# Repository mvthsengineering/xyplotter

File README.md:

# xyplotter
An X-Y plotter with stepper motors for both axis and stepper control for pen height.

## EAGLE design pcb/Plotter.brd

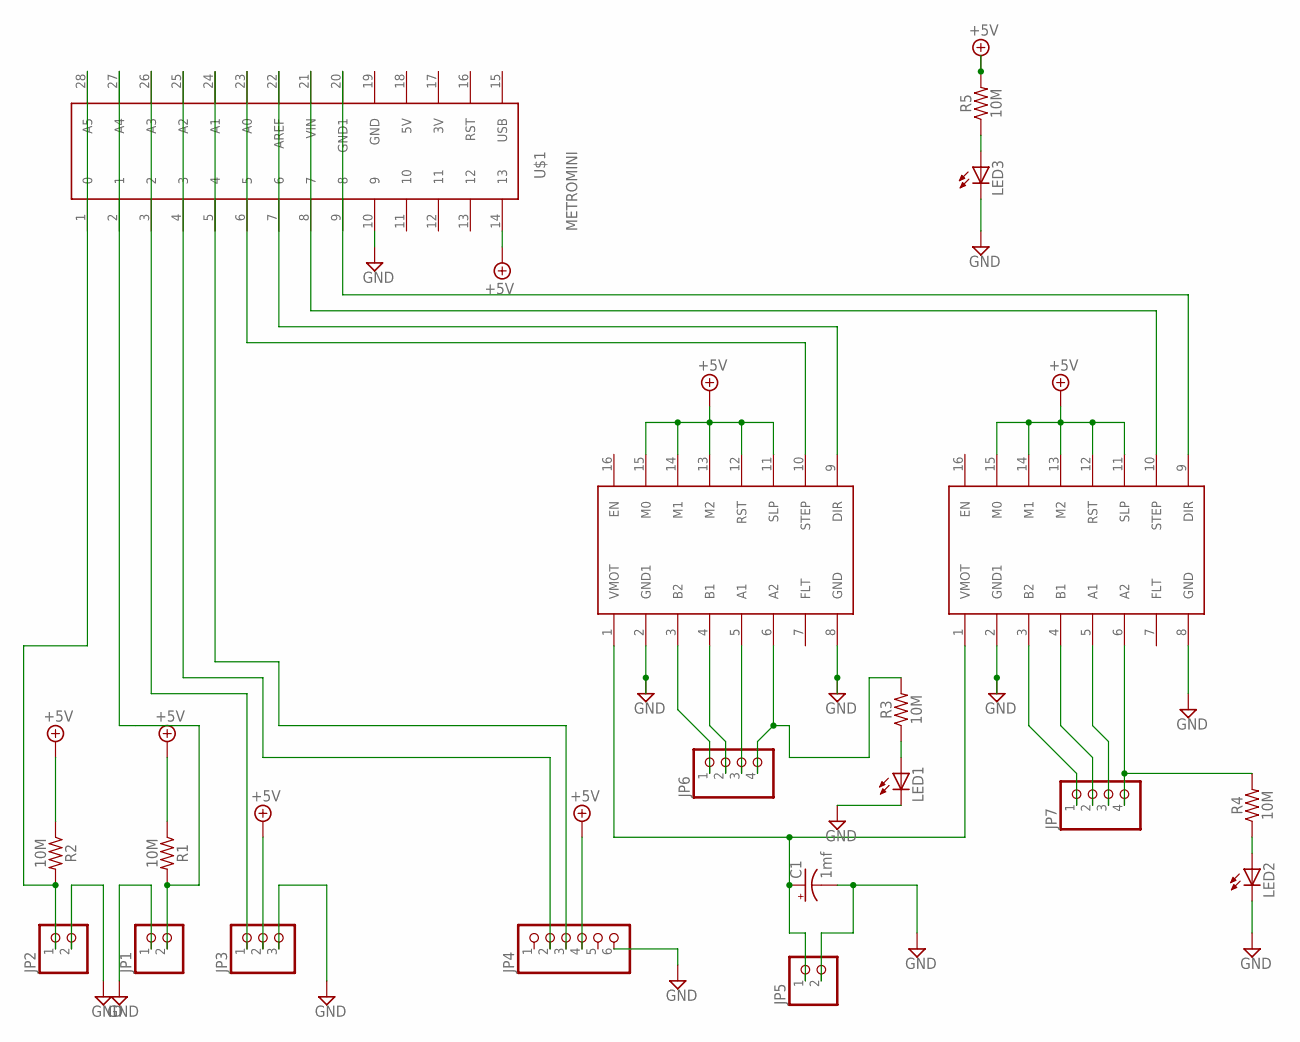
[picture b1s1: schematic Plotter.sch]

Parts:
C1: 1mf; CPOL-RADIAL-5MM-10MM-KIT
JP1, JP2, JP5: PINHD-1X2; 1X02
JP3: PINHD-1X3; 1X03
JP4: PINHD-1X6; 1X06
JP6, JP7: PINHD-1X4; 1X04
LED1, LED2, LED3: LED_ELD260; LED_LD260
R1, R2, R3, R4, R5: 10M; AXIAL-0.3
U$1: METROMINI
U$2, U$3: DRV8825

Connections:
+5V: JP3.2, JP4.4, R1.P$1 (1), R2.P$1 (1), R5.P$2 (2), U$1.14 (13), U$2.11 (SLP), U$2.12 (RST), U$2.13 (M2), U$2.14 (M1), U$2.15 (M0), U$3.11 (SLP), U$3.12 (RST), U$3.13 (M2), U$3.14 (M1), U$3.15 (M0)
GND: C1.-, JP1.1, JP2.2, JP3.3, JP4.6, JP5.2, LED1.K (C), LED2.K (C), LED3.K (C), U$1.10 (9), U$2.2 (GND1), U$2.8 (GND), U$3.2 (GND1), U$3.8 (GND)
unnamed: JP1.2, R1.P$2 (2), U$1.27 (A4)
unnamed: JP2.1, R2.P$2 (2), U$1.28 (A5)
unnamed: LED1.A, R3.P$1 (1)
unnamed: LED2.A, R4.P$1 (1)
unnamed: JP3.1, U$1.26 (A3)
unnamed: LED3.A, R5.P$1 (1)
unnamed: JP4.2, U$1.25 (A2)
unnamed: C1.+, JP5.1, U$2.1 (VMOT), U$3.1 (VMOT)
unnamed: JP4.3, U$1.24 (A1)
unnamed: JP6.1, U$2.3 (B2)
unnamed: JP6.2, U$2.4 (B1)
unnamed: JP6.3, U$2.5 (A1)
unnamed: JP6.4, R3.P$2 (2), U$2.6 (A2)
unnamed: JP7.1, U$3.3 (B2)
unnamed: JP7.2, U$3.4 (B1)
unnamed: JP7.3, U$3.5 (A1)
unnamed: JP7.4, R4.P$2 (2), U$3.6 (A2)
unnamed: U$1.21 (VIN), U$3.10 (STEP)
unnamed: U$1.23 (A0), U$2.10 (STEP)
unnamed: U$1.22 (AREF), U$2.9 (DIR)
unnamed: U$1.20 (GND1), U$3.9 (DIR)

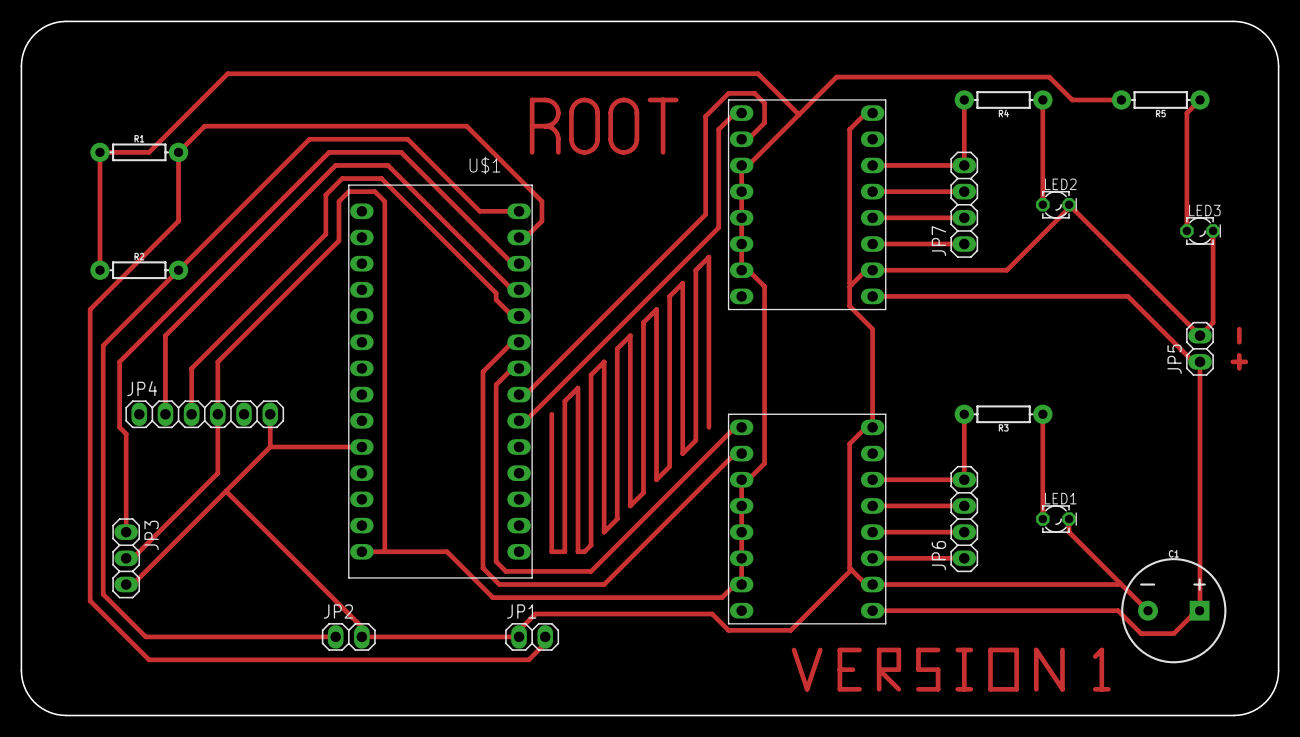
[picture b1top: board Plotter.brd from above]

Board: 2 copper layers, 121.9 x 67.3 mm, 19 parts (0 on the bottom side), 23 nets.

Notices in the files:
parts and their libraries:
SparkFun-Resistors: Licensing: Creative Commons ShareAlike 4.0 International - https://creativecommons.org/licenses/by-sa/4.0
